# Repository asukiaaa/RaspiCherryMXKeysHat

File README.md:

# RaspiCherryMXKeysHat
A Raspberry Pi Hat for Cherry MX Keys.

# Connections

Switch | Pin
--- | ---
SW1 | GPIO17
SW2 | GPIO18
SW3 | GPIO22
SW4 | GPIO23
SW5 | GPIO24
SW6 | GPIO25

# License
MIT

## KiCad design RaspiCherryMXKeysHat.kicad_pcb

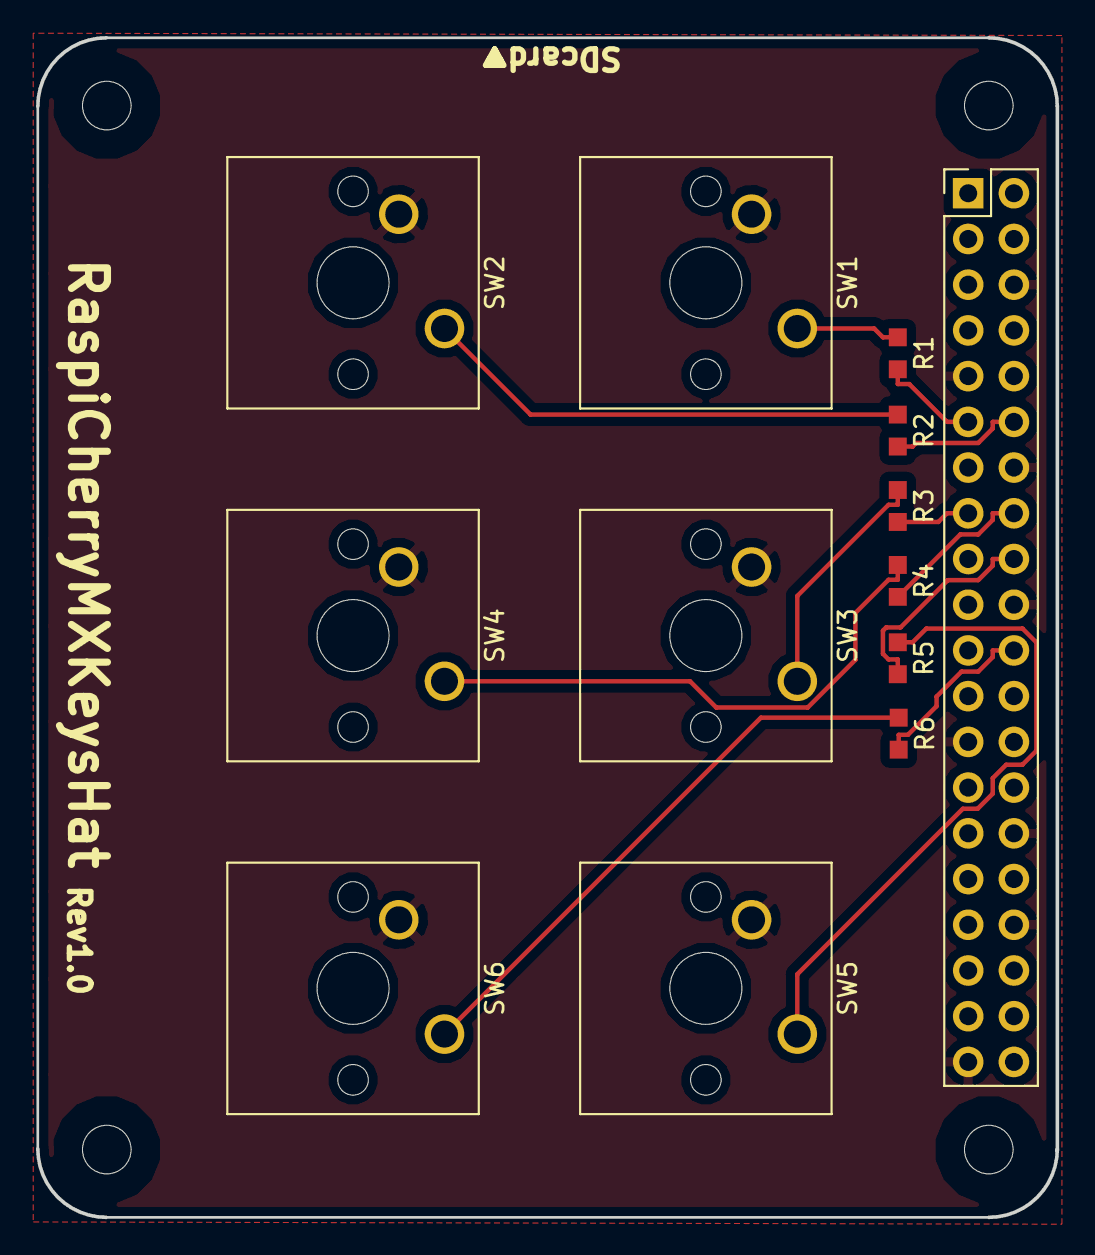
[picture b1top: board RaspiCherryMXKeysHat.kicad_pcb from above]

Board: 2 copper layers, 56.6 x 65.5 mm, 17 parts (0 on the bottom side), 13 nets.

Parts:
J1: Raspberry_Pi_2_3; PinHeader_2x20_P2.54mm_Vertical
R1, R2, R3, R4, R5, R6: R; R_0603_1608Metric_Pad0.99x1.00mm_HandSolder
REF1, REF2, REF3, REF4: MountingHole_2.7mm; LargeClearanceMountingHole_2.7mm
SW1, SW2, SW3, SW4, SW5, SW6: SW_Push; SW_Cherry_MX1A_1.00u_PCB

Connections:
GND: J1.6, J1.9, J1.14, J1.20, J1.25, J1.30, J1.34, J1.39, SW1.2, SW2.2, SW3.2, SW4.2, SW5.2, SW6.2
GPIO17(GEN0): J1.11, R1.2
GPIO18(GEN1): J1.12, R2.2
GPIO22(GEN3): J1.15, R3.2
GPIO23(GEN4): J1.16, R4.2
GPIO24(GEN5): J1.18, R5.2
GPIO25(GEN6): J1.22, R6.2
unnamed: R1.1, SW1.1
unnamed: R2.1, SW2.1
unnamed: R3.1, SW3.1
unnamed: R4.1, SW4.1
unnamed: R5.1, SW5.1
unnamed: R6.1, SW6.1

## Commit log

2018-05-22 Add pin connection info to readme
2018-05-24 Add cover plates data
2018-05-26 Update top plate cut line position
